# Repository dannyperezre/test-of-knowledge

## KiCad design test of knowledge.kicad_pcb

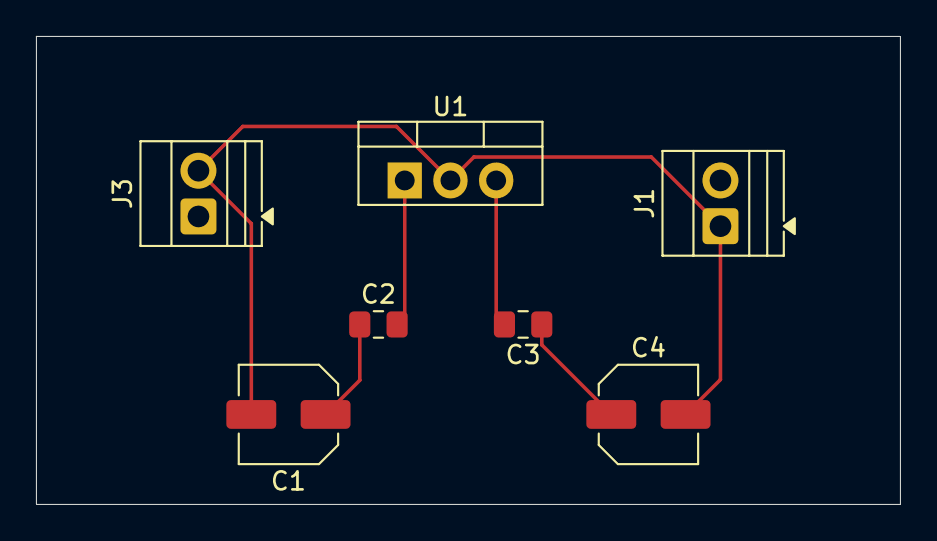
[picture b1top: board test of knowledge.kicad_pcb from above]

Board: 2 copper layers, 48.0 x 26.0 mm, 7 parts (0 on the bottom side), 5 nets.

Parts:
C1, C4: 47uF; C_Elec_5x5.4
C2, C3: 0.1 uF; C_0805_2012Metric_Pad1.18x1.45mm_HandSolder
J1, J3: Screw_Terminal_01x02; TerminalBlock_Xinya_XY308-2.54-2P_1x02_P2.54mm_Horizontal
U1: LM7805_TO220; TO-220-3_Vertical

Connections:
GND: C1.2, C4.2, J1.1, J3.2, U1.2 (GND)
unnamed: C1.1, C2.1
unnamed: C3.1, C4.1
unnamed: C2.2, U1.1 (VI)
unnamed: C3.2, U1.3 (VO)
